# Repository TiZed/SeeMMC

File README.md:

## SeeMMC - A SD-Card adaptor for eMMC ICs

A small project to connect onboard eMMC ICs to an SD-Card slot.

The adaptor includes a level translator and 1.8V supply, to prevent damage to other board components.

This will only work for boards that have accessible eMMC signals, and can prevent onboard CPU from intervening.

To fit in a SD card slot, this design has to be manufactured with a PCB thickness of 1.2mm, not the default 1.6mm.

Successfully manufactured and tested, managed to extract the FW of a Samsung TV.

---
<br />This work is licensed under a <a rel="license" href="http://creativecommons.org/licenses/by-nc-sa/4.0/">Creative Commons Attribution-NonCommercial-ShareAlike 4.0 International License</a>.

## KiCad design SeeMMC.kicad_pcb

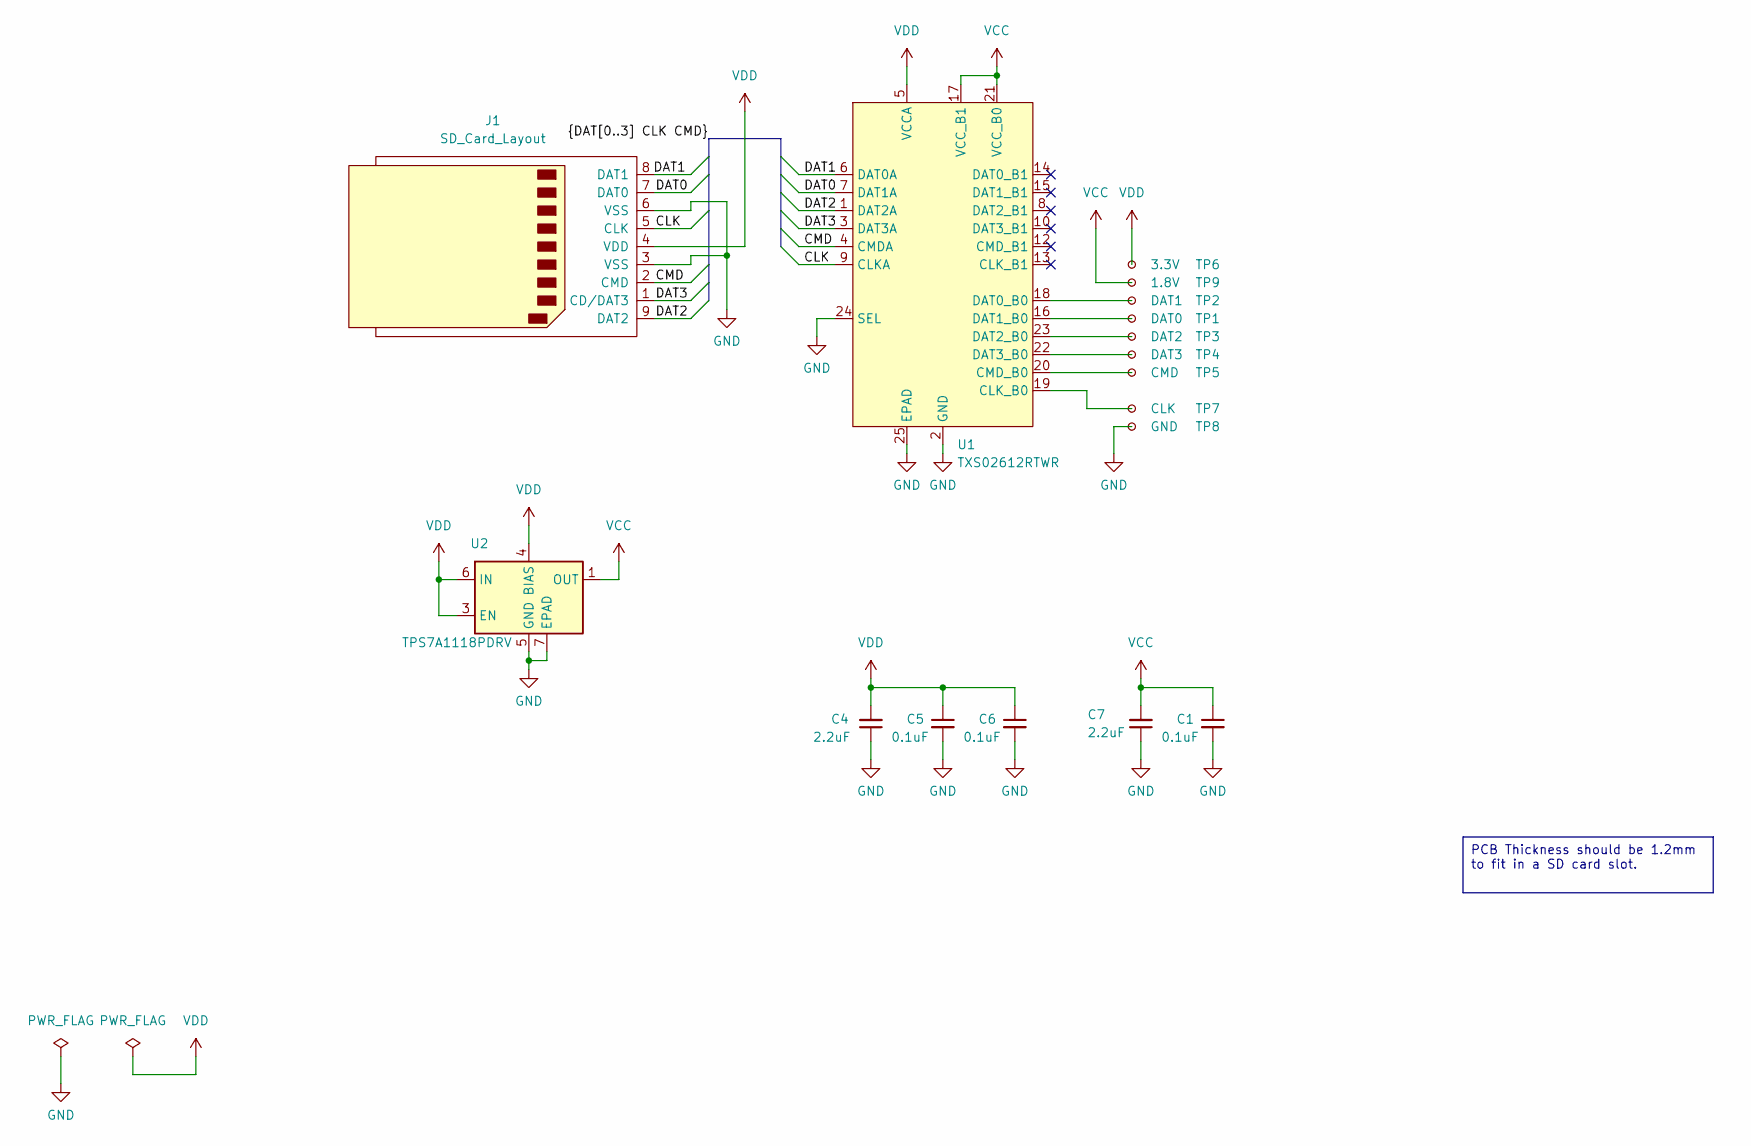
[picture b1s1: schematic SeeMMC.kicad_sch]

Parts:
C1, C5, C6: 0.1uF; C_0402_1005Metric
C4, C7: 2.2uF; C_0402_1005Metric
J1: SD_Card_Layout
TP1: DAT0; TestPoint_Pad_D2.0mm
TP2: DAT1; TestPoint_Pad_D2.0mm
TP3: DAT2; TestPoint_Pad_D2.0mm
TP4: DAT3; TestPoint_Pad_D2.0mm
TP5: CMD; TestPoint_Pad_D2.0mm
TP6: 3.3V; TestPoint_Pad_D2.0mm
TP7: CLK; TestPoint_Pad_D2.0mm
TP8: GND; TestPoint_Pad_D2.0mm
TP9: 1.8V; TestPoint_Pad_D2.0mm
U1: TXS02612RTWR; WQFN-24-1EP_4x4mm_P0.5mm_EP2.45x2.45mm_ThermalVias
U2: TPS7A1118PDRV; WSON-6-1EP_2x2mm_P0.65mm_EP1x1.6mm_ThermalVias

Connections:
/CLK: J1.5 (CLK), U1.9 (CLKA)
/CMD: J1.2 (CMD), U1.4 (CMDA)
/DAT0: J1.7 (DAT0), U1.7 (DAT1A)
/DAT1: J1.8 (DAT1), U1.6 (DAT0A)
/DAT2: J1.9 (DAT2), U1.1 (DAT2A)
/DAT3: J1.1 (CD/DAT3), U1.3 (DAT3A)
GND: C1.2, C4.1, C5.2, C6.2, C7.1, J1.3 (VSS), J1.6 (VSS), TP8.1, U1.2 (GND), U1.11 (GND), U1.24 (SEL), U1.25 (EPAD), U2.5 (GND), U2.7 (EPAD)
unnamed: TP7.1, U1.19 (CLK_B0)
unnamed: TP5.1, U1.20 (CMD_B0)
unnamed: TP2.1, U1.18 (DAT0_B0)
unnamed: TP1.1, U1.16 (DAT1_B0)
unnamed: TP3.1, U1.23 (DAT2_B0)
unnamed: TP4.1, U1.22 (DAT3_B0)
VCC: C1.1, C7.2, TP9.1, U1.17 (VCC_B1), U1.21 (VCC_B0), U2.1 (OUT)
VDD: C4.2, C5.1, C6.1, J1.4 (VDD), TP6.1, U1.5 (VCCA), U2.3 (EN), U2.4 (BIAS), U2.6 (IN)

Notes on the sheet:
PCB Thickness should be 1.2mm to fit in a SD card slot.

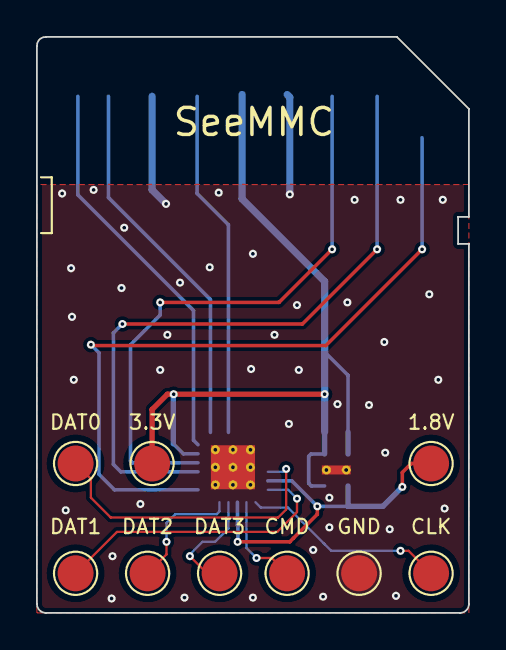
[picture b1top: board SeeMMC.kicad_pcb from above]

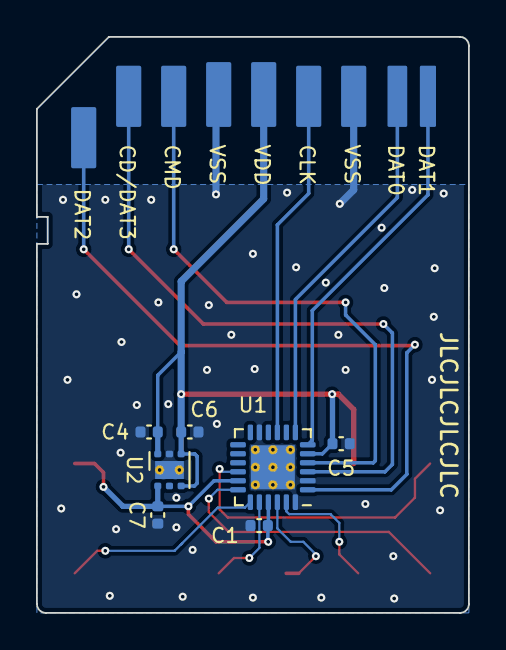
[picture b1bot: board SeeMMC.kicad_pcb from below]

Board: 2 copper layers, 24.0 x 32.0 mm, 17 parts (7 on the bottom side), 15 nets.

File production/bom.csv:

Designator,Footprint,Quantity,Value,LCSC Part #
"C1, C5, C6",0402,3,0.1uF,
"C4, C7",0402,2,2.2uF,
J1,SD_Card_Layout,1,SD_Card,
TP1,TestPoint_Pad_D2.0mm,1,DAT0,
TP2,TestPoint_Pad_D2.0mm,1,DAT1,
TP3,TestPoint_Pad_D2.0mm,1,DAT2,
TP4,TestPoint_Pad_D2.0mm,1,DAT3,
TP5,TestPoint_Pad_D2.0mm,1,CMD,
TP6,TestPoint_Pad_D2.0mm,1,3.3V,
TP7,TestPoint_Pad_D2.0mm,1,CLK,
TP8,TestPoint_Pad_D2.0mm,1,GND,
TP9,TestPoint_Pad_D2.0mm,1,1.8V,
U1,WQFN-24-1EP_4x4mm_P0.5mm_EP2.45x2.45mm_ThermalVias,1,TXS02612RTWR,
U2,WSON-6-1EP_2x2mm_P0.65mm_EP1x1.6mm_ThermalVias,1,TPS7A1118PDRV,

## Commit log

2023-07-05 Adding project
2023-07-05 Some cosmetic changes
2023-07-05 README update
2023-07-05 Production ready
2023-07-06 Added external dimensions
2023-09-09 Updated after building and testing
2024-05-10 Updated KiCad version
